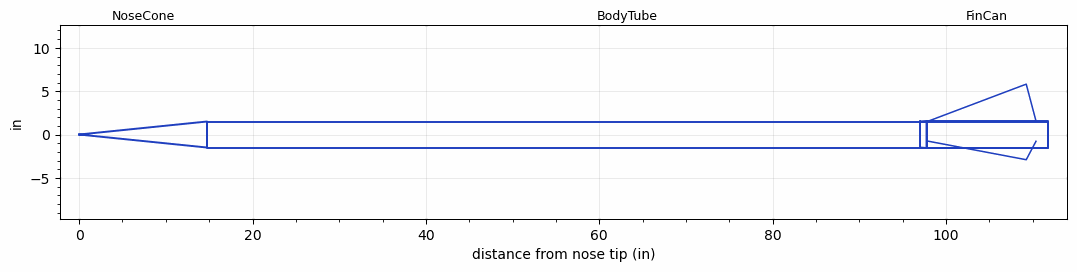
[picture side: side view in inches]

<RASAeroDocument>
 <FileVersion>2</FileVersion>
 <RocketDesign>
  <NoseCone>
   <Length>14.75</Length>
   <Diameter>3</Diameter>
   <Shape>Conical</Shape>
   <BluntRadius>0.031</BluntRadius>
   <Location>0</Location>
  </NoseCone>
  <BodyTube>
   <Length>97</Length>
   <Diameter>3</Diameter>
   <Location>14.75</Location>
  </BodyTube>
  <FinCan>
   <Length>14</Length>
   <Diameter>3.125</Diameter>
   <InsideDiameter>3</InsideDiameter>
   <LaunchShoeArea>0.15</LaunchShoeArea>
   <Location>111.75</Location>
   <ShoulderLength>0.75</ShoulderLength>
   <Offset>-14</Offset>
   <Fin>
    <Count>3</Count>
    <Chord>12.375</Chord>
    <Span>4.25</Span>
    <SweepDistance>11.25</SweepDistance>
    <TipChord>0</TipChord>
    <Thickness>0.188</Thickness>
    <Location>13.75</Location>
    <AirfoilSection>Rounded</AirfoilSection>
   </Fin>
  </FinCan>
  <Surface>Smooth (Zero Roughness)</Surface>
  <ModifiedBarrowman>False</ModifiedBarrowman>
  <Turbulence>False</Turbulence>
  <SustainerNozzle>1.188</SustainerNozzle>
  <UseBooster1>False</UseBooster1>
  <UseBooster2>False</UseBooster2>
  <Comments>Rabia
Ray Kinsel
Rocket launched 3 May 2008
ALX1 file rocket data provided by Ray Kinsel

Barometric Altimeter
Altitude = 12745 ft

RASAero II Prediction = 12197 ft
Error = -4.30%
</Comments>
 </RocketDesign>
 <LaunchSite>
  <Altitude>2400</Altitude>
  <Pressure>30.05</Pressure>
  <RodAngle>0</RodAngle>
  <RodLength>10</RodLength>
  <Temperature>80</Temperature>
  <WindSpeed>8</WindSpeed>
 </LaunchSite>
 <Recovery>
  <Altitude1>1000</Altitude1>
  <Altitude2>750</Altitude2>
  <DeviceType1>Parachute</DeviceType1>
  <DeviceType2>Parachute</DeviceType2>
  <Event1>True</Event1>
  <Event2>True</Event2>
  <Size1>12</Size1>
  <Size2>60</Size2>
  <EventType1>Apogee</EventType1>
  <EventType2>Altitude</EventType2>
  <CD1>1.33</CD1>
  <CD2>1.33</CD2>
 </Recovery>
 <SimulationList>
  <Simulation>
   <SustainerEngine>L1080BB  (AMW)</SustainerEngine>
   <SustainerLaunchWt>18.44</SustainerLaunchWt>
   <SustainerNozzleDiameter>1.188</SustainerNozzleDiameter>
   <SustainerCG>61.5</SustainerCG>
   <SustainerIgnitionDelay>0</SustainerIgnitionDelay>
   <Booster1SeparationDelay>0</Booster1SeparationDelay>
   <Booster1IgnitionDelay>0</Booster1IgnitionDelay>
   <IncludeBooster1>False</IncludeBooster1>
   <Booster2Delay>0</Booster2Delay>
   <IncludeBooster2>False</IncludeBooster2>
   <TimetoApogee>25.23048</TimetoApogee>
   <MaxAltitude>12197.07</MaxAltitude>
   <MaxVelocity>1321.267</MaxVelocity>
  </Simulation>
 </SimulationList>
</RASAeroDocument>
